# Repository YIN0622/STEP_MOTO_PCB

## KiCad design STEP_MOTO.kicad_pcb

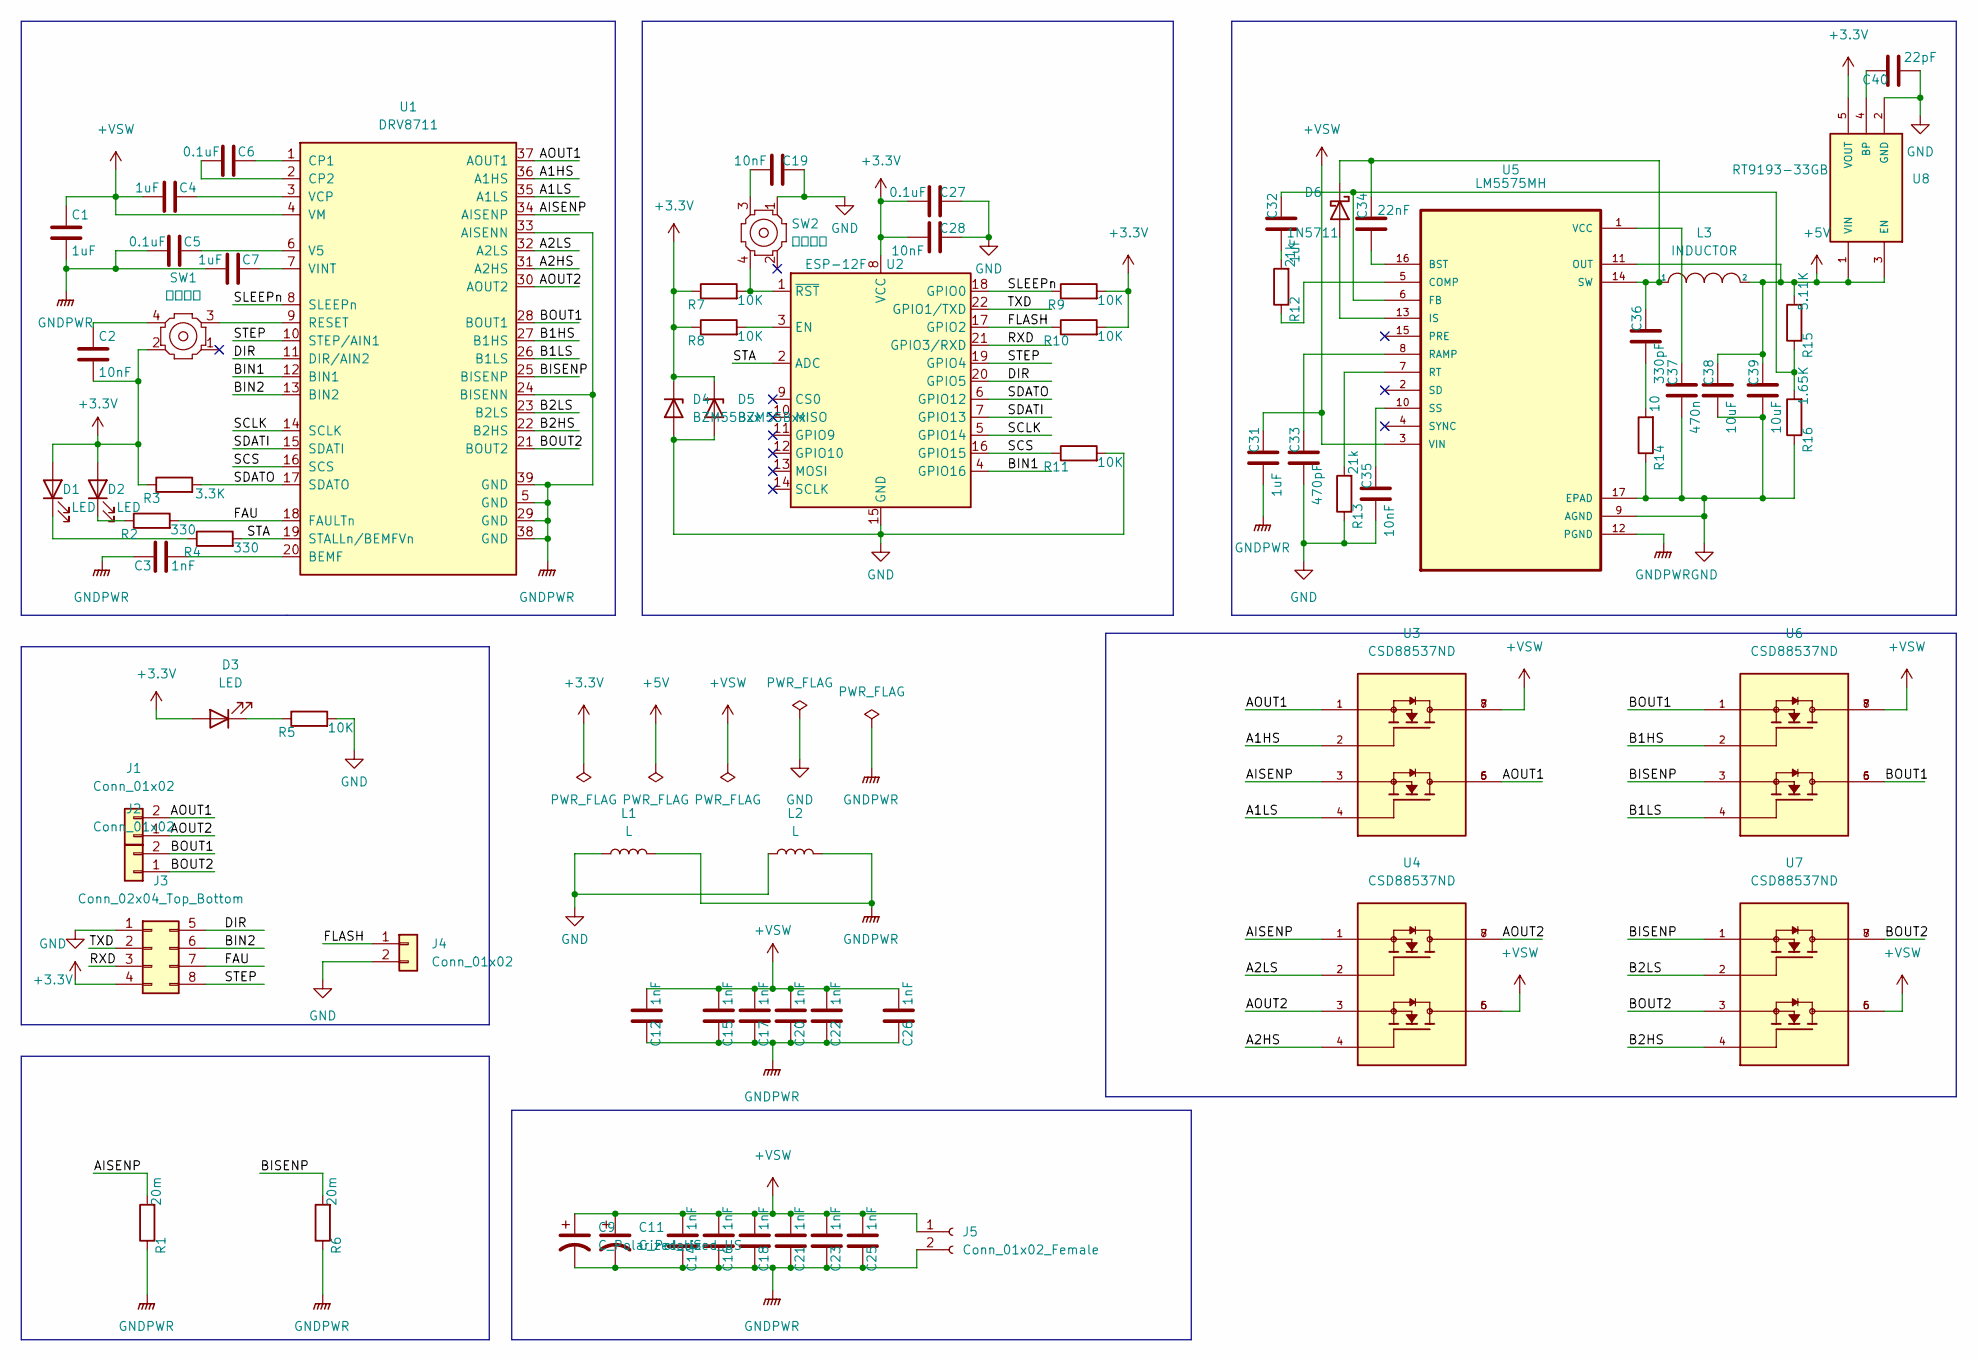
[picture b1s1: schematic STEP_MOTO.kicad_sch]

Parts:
C1, C4, C31: 1uF; C_1206_3216Metric_Pad1.33x1.80mm_HandSolder
C2, C19, C28, C35: 10nF; C_0603_1608Metric_Pad1.08x0.95mm_HandSolder
C3: 1nF; C_0603_1608Metric_Pad1.08x0.95mm_HandSolder
C5, C6, C27: 0.1uF; C_0603_1608Metric_Pad1.08x0.95mm_HandSolder
C7, C32: 1uF; C_0603_1608Metric_Pad1.08x0.95mm_HandSolder
C9, C11: C_Polarized_US; CP_Elec_8x10.5
C12, C14, C15, C16, C17, C18, C20, C21, C22, C23, C25, C26: 1nF; C_1206_3216Metric_Pad1.33x1.80mm_HandSolder
C33: 470pF; C_0603_1608Metric_Pad1.08x0.95mm_HandSolder
C34: 22nF; C_0603_1608Metric_Pad1.08x0.95mm_HandSolder
C36: 330pF; C_0603_1608Metric_Pad1.08x0.95mm_HandSolder
C37: 470n; C_0603_1608Metric_Pad1.08x0.95mm_HandSolder
C38, C39: 10uF; C_0603_1608Metric_Pad1.08x0.95mm_HandSolder
C40: 22pF; C_0603_1608Metric_Pad1.08x0.95mm_HandSolder
D1, D2, D3: LED; LED_0805_2012Metric_Pad1.15x1.40mm_HandSolder
D4, D5: BZM55Bxx; DIO_LL4148-13
D6: 1N5711; D_SMB_Handsoldering
J1, J2: Conn_01x02; 螺钉式接线端子5.0
J3: Conn_02x04_Top_Bottom; PinHeader_2x04_P2.54mm_Vertical
J4: Conn_01x02; PinHeader_1x02_P2.54mm_Vertical
J5: Conn_01x02_Female; 螺钉式接线端子5.0
L1, L2: L; C_0805_2012Metric_Pad1.18x1.45mm_HandSolder
L3: INDUCTOR; L_12x12mm_H8mm
R1, R6: 20m; R_2512_6332Metric_Pad1.40x3.35mm_HandSolder
R2, R4: 330; R_0603_1608Metric_Pad0.98x0.95mm_HandSolder
R3: 3.3K; R_0603_1608Metric_Pad0.98x0.95mm_HandSolder
R5, R7, R8, R9, R10, R11: 10K; R_0603_1608Metric_Pad0.98x0.95mm_HandSolder
R12, R13: 21k; R_0603_1608Metric_Pad0.98x0.95mm_HandSolder
R14: 10; R_0603_1608Metric_Pad0.98x0.95mm_HandSolder
R15: 5.11K; R_0603_1608Metric_Pad0.98x0.95mm_HandSolder
R16: 1.65K; R_0603_1608Metric_Pad0.98x0.95mm_HandSolder
SW1, SW2: 轻触开关; KEY-SMD_4P-L5.2-W5.2
U1: DRV8711; IC_DRV8711DCP
U2: ESP-12F; ESP-12E
U3, U4, U6, U7: CSD88537ND; SOIC127P599X175-8N; PARTREV A
U5: LM5575MH; SOP65P640X120-17N
U8: RT9193-33GB; SOT94P279X129-5N

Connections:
+3.3V: C2.1, C27.2, C28.2, D1.2 (A), D2.2 (A), D3.2 (A), D4.1 (K), D5.1 (K), J3.4, R3.1, R7.1, R8.1, R9.2, R10.2, SW1.2, U2.8 (VCC), U8.5 (VOUT)
+5V: C38.1, C39.1, L3.2, R15.2, U5.11 (OUT), U8.1 (VIN), U8.3 (EN)
+VSW: C1.2, C4.1, C9.1, C11.1, C12.1, C14.1, C15.1, C16.1, C17.1, C18.1, C20.1, C21.1, C22.1, C23.1, C25.1, C26.1, C31.1, J5.1, U1.4 (VM), U3.7, U3.8, U4.5, U4.6, U5.3 (VIN), U6.7, U6.8, U7.5, U7.6
/A1HS: U1.36 (A1HS), U3.2
/A1LS: U1.35 (A1LS), U3.4
/A2HS: U1.31 (A2HS), U4.4
/A2LS: U1.32 (A2LS), U4.2
/AISENP: R1.2, U1.34 (AISENP), U3.3, U4.1
/AOUT1: J1.2, U1.37 (AOUT1), U3.1, U3.5, U3.6
/AOUT2: J1.1, U1.30 (AOUT2), U4.3, U4.7, U4.8
/B1HS: U1.27 (B1HS), U6.2
/B1LS: U1.26 (B1LS), U6.4
/B2HS: U1.22 (B2HS), U7.4
/B2LS: U1.23 (B2LS), U7.2
/BIN1: U1.12 (BIN1), U2.4 (GPIO16)
/BIN2: J3.6, U1.13 (BIN2)
/BISENP: R6.2, U1.25 (BISENP), U6.3, U7.1
/BOUT1: J2.2, U1.28 (BOUT1), U6.1, U6.5, U6.6
/BOUT2: J2.1, U1.21 (BOUT2), U7.3, U7.7, U7.8
/DIR: J3.5, U1.11 (DIR/AIN2), U2.20 (GPIO5)
/FAU: J3.7, R2.2, U1.18 (FAULTn)
/FLASH: J4.1, R10.1, U2.17 (GPIO2)
/RXD: J3.3, U2.21 (GPIO3/RXD)
/SCLK: U1.14 (SCLK), U2.5 (GPIO14)
/SCS: R11.1, U1.16 (SCS), U2.16 (GPIO15)
/SDATI: U1.15 (SDATI), U2.7 (GPIO13)
/SDATO: R3.2, U1.17 (SDATO), U2.6 (GPIO12)
/SLEEPn: R9.1, U1.8 (SLEEPn), U2.18 (GPIO0)
/STA: R4.2, U1.19 (STALLn/BEMFVn), U2.2 (ADC)
/STEP: J3.8, U1.10 (STEP/AIN1), U2.19 (GPIO4)
/TXD: J3.2, U2.22 (GPIO1/TXD)
GND: C19.1, C27.1, C28.1, C33.2, C35.2, C37.2, C38.2, C39.2, C40.2, D4.2 (A), D5.2 (A), J3.1, J4.2, L1.1, L2.1, R5.2, R11.2, R13.1, R14.1, R16.1, SW2.1, U2.15 (GND), U5.9 (AGND), U5.17 (EPAD), U8.2 (GND)
GNDPWR: C1.1, C3.2, C5.1, C7.1, C9.2, C11.2, C12.2, C14.2, C15.2, C16.2, C17.2, C18.2, C20.2, C21.2, C22.2, C23.2, C25.2, C26.2, C31.2, J5.2, L1.2, L2.2, R1.1, R6.1, U1.5 (GND), U1.24 (BISENN), U1.29 (GND), U1.33 (AISENN), U1.38 (GND), U1.39 (GND), U5.12 (PGND)
unnamed: C2.2, SW1.4
unnamed: C3.1, U1.20 (BEMF)
unnamed: C4.2, U1.3 (VCP)
unnamed: C5.2, U1.6 (V5)
unnamed: C6.1, U1.1 (CP1)
unnamed: C6.2, U1.2 (CP2)
unnamed: C7.2, U1.7 (VINT)
unnamed: C19.2, SW2.3
unnamed: C32.1, R15.1, R16.2, U5.6 (FB)
unnamed: C32.2, R12.2
unnamed: C33.1, U5.8 (RAMP)
unnamed: C34.1, C36.1, D6.1 (K), L3.1, U5.14 (SW)
unnamed: C34.2, U5.16 (BST)
unnamed: C35.1, U5.10 (SS)
unnamed: C36.2, R14.2
unnamed: C37.1, U5.1 (VCC)
unnamed: C40.1, U8.4 (BP)
unnamed: D1.1 (K), R4.1
unnamed: D2.1 (K), R2.1
unnamed: D3.1 (K), R5.1
unnamed: D6.2 (A), U5.13 (IS)
unnamed: R7.2, SW2.4, U2.1 (~RST)
unnamed: R8.2, U2.3 (EN)
unnamed: R12.1, U5.5 (COMP)
unnamed: R13.2, U5.7 (RT)
unnamed: SW1.3, U1.9 (RESET)

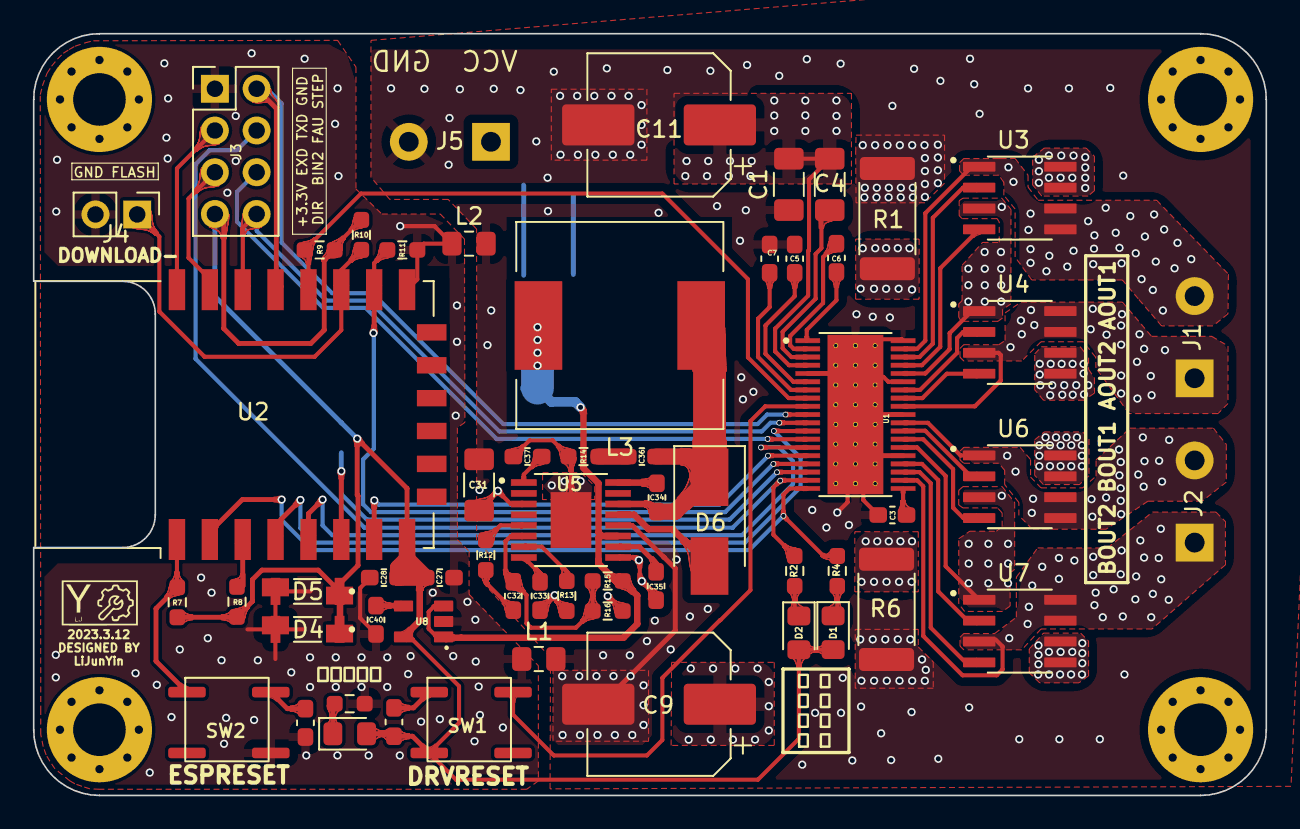
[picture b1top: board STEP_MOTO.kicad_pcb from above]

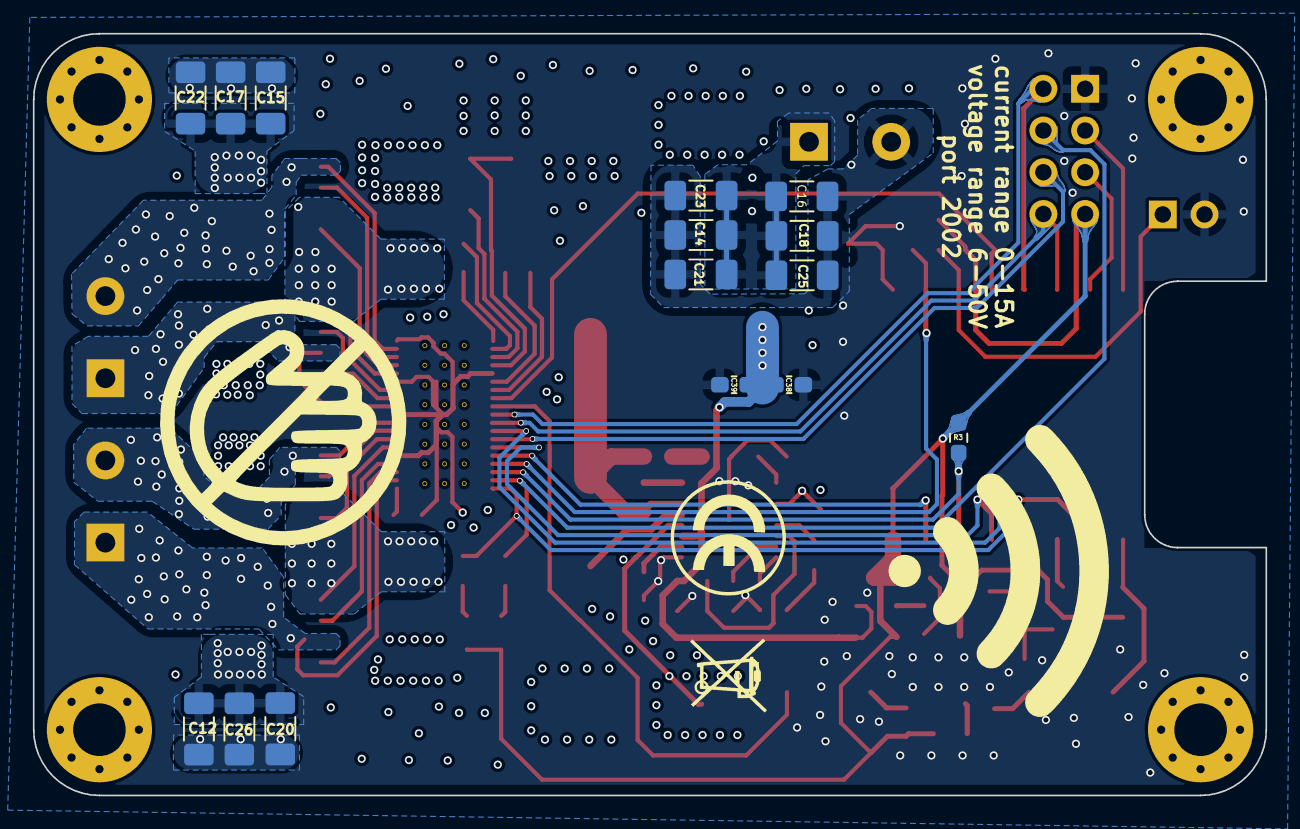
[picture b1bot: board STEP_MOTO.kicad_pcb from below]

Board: 4 copper layers, 75.0 x 46.4 mm, 74 parts (15 on the bottom side), 59 nets.

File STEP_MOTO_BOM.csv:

"Comment","Description","Designator","Footprint","LibRef","Pins","Quantity","PartNumber","url",
"1uF","desc","C1,C4,C31,","C_1206_3216Metric_Pad1.33x1.80mm_HandSolder","libref","2","3","","",
"10nF","desc","C2,C19,C28,C35,","C_0603_1608Metric_Pad1.08x0.95mm_HandSolder","libref","2","4","","",
"1nF","desc","C3,","C_0603_1608Metric_Pad1.08x0.95mm_HandSolder","libref","2","1","","",
"0.1uF","desc","C5,C6,C27,","C_0603_1608Metric_Pad1.08x0.95mm_HandSolder","libref","2","3","","",
"1uF","desc","C7,C32,","C_0603_1608Metric_Pad1.08x0.95mm_HandSolder","libref","2","2","","",
"C_Polarized_US","desc","C9,C11,","CP_Elec_8x10.5","libref","2","2","","",
"470pF","desc","C33,","C_0603_1608Metric_Pad1.08x0.95mm_HandSolder","libref","2","1","","",
"22nF","desc","C34,","C_0603_1608Metric_Pad1.08x0.95mm_HandSolder","libref","2","1","","",
"330pF","desc","C36,","C_0603_1608Metric_Pad1.08x0.95mm_HandSolder","libref","2","1","","",
"470n","desc","C37,","C_0603_1608Metric_Pad1.08x0.95mm_HandSolder","libref","2","1","","",
"22pF","desc","C40,","C_0603_1608Metric_Pad1.08x0.95mm_HandSolder","libref","2","1","","",
"LED","desc","D1,D2,D3,","LED_0805_2012Metric_Pad1.15x1.40mm_HandSolder","libref","2","3","","",
"BZM55Bxx","desc","D4,D5,","DIO_LL4148-13","libref","2","2","","",
"1N5711","desc","D6,","D_SMB_Handsoldering","libref","2","1","","",
"L","desc","L1,L2,","C_0805_2012Metric_Pad1.18x1.45mm_HandSolder","libref","2","2","","",
"INDUCTOR","desc","L3,","L_12x12mm_H8mm","libref","2","1","","",
"20m","desc","R1,R6,","R_2512_6332Metric_Pad1.40x3.35mm_HandSolder","libref","2","2","","",
"330","desc","R2,R4,","R_0603_1608Metric_Pad0.98x0.95mm_HandSolder","libref","2","2","","",
"10K","desc","R5,R7,R8,R9,R10,R11,","R_0603_1608Metric_Pad0.98x0.95mm_HandSolder","libref","2","6","","",
"21k","desc","R12,R13,","R_0603_1608Metric_Pad0.98x0.95mm_HandSolder","libref","2","2","","",
"10","desc","R14,","R_0603_1608Metric_Pad0.98x0.95mm_HandSolder","libref","2","1","","",
"5.11K","desc","R15,","R_0603_1608Metric_Pad0.98x0.95mm_HandSolder","libref","2","1","","",
"1.65K","desc","R16,","R_0603_1608Metric_Pad0.98x0.95mm_HandSolder","libref","2","1","","",
"ESP-12F","desc","U2,","ESP-12E","libref","22","1","","",
"CSD88537ND","desc","U3,U4,U6,U7,","SOIC127P599X175-8N","libref","8","4","","",
"LM5575MH","desc","U5,","SOP65P640X120-17N","libref","17","1","","",
"RT9193-33GB","desc","U8,","SOT94P279X129-5N","libref","5","1","","",
"轻触开关","desc","SW1,SW2,","KEY-SMD_4P-L5.2-W5.2","libref","4","2","","",
"LOGO","desc","G***,","wifi","libref","0","1","","",
"LOGO","desc","G***,","logo1","libref","0","1","","",
"1nF","desc","C12,C14,C15,C16,C17,C18,C20,C21,C22,C23,C25,C26,","C_1206_3216Metric_Pad1.33x1.80mm_HandSolder","libref","2","12","","",
"10uF","desc","C38,C39,","C_0603_1608Metric_Pad1.08x0.95mm_HandSolder","libref","2","2","","",
"3.3K","desc","R3,","R_0603_1608Metric_Pad0.98x0.95mm_HandSolder","libref","2","1","","",
"LOGO","desc","G***,","do not touch","libref","0","1","","",
"LOGO","desc","G***,","ce","libref","0","1","","",
"LOGO","desc","G***,","不可回收","libref","0","1","","",
"Through Hole Items ",
"Conn_01x02","desc","J1,J2,","螺钉式接线端子5.0","libref","2","2","","",
"Conn_02x04_Top_Bottom","desc","J3,","PinHeader_2x04_P2.54mm_Vertical","libref","8","1","","",
"Conn_01x02","desc","J4,","PinHeader_1x02_P2.54mm_Vertical","libref","2","1","","",
"Conn_01x02_Female","desc","J5,","螺钉式接线端子5.0","libref","2","1","","",
"DRV8711","desc","U1,","IC_DRV8711DCP","libref","63","1","","",
"MountingHole_3.2mm_M3_Pad_Via","desc","REF**,REF**,REF**,REF**,","MountingHole_3.2mm_M3_Pad_Via","libref","9","4","","",

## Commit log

2023-03-12 V1.0
2023-03-13 v1.1暂存版
